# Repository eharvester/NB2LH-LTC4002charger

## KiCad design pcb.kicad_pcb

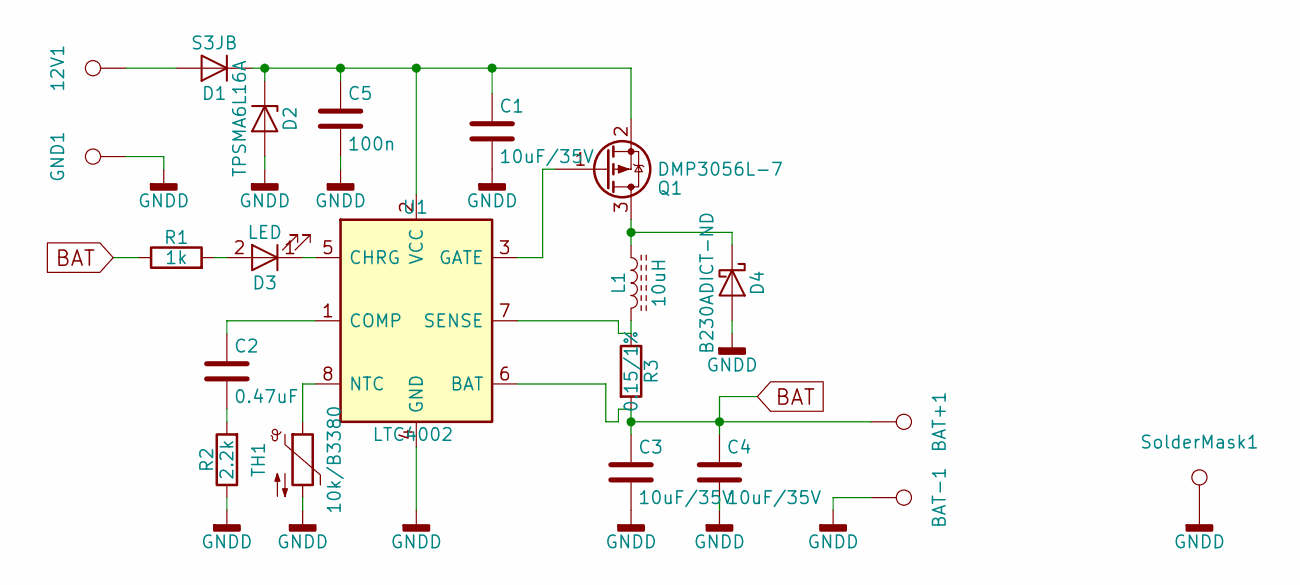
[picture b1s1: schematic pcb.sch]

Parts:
12V1: TEST_1P; TerminalPad3x8
BAT+1: TEST_1P; TerminalPad3x8
BAT-1: TEST_1P; TerminalPad3x8
C1, C3, C4: 10uF/35V; C_1206
C2: 0.47uF; C_0603
C5: 100n; C_0603
D1: S3JB; D_SMB
D2: TPSMA6L16A; D_SMA
D3: LED; R_1206_HandSoldering
D4: B230ADICT-ND; D_SMB
GND1: TEST_1P; TerminalPad3x8
L1: 10uH; L_1210
Q1: DMP3056L-7; SOT-23
R1: 1k; R_0603
R2: 2.2k; R_0603
R3: 0.15/1%; R_0603
SolderMask1: TEST_1P; SolderMask
TH1: 10k/B3380; R_1206_HandSoldering
U1: LTC4002; SOIC-8_3.9x4.9mm_Pitch1.27mm

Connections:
BAT: BAT+1.1, C3.1, C4.1, R1.1, R3.2, U1.6 (BAT)
GNDD: BAT-1.1, C1.2, C3.2, C4.2, C5.2, D2.2 (A), D4.2 (A), GND1.1, R2.1, SolderMask1.1, TH1.2, U1.4 (GND)
unnamed: 12V1.1, D1.2 (A)
unnamed: C1.1, C5.1, D1.1 (K), D2.1 (K), Q1.2 (S), U1.2 (VCC)
unnamed: C2.1, U1.1 (COMP)
unnamed: C2.2, R2.2
unnamed: D3.1 (K), U1.5 (CHRG)
unnamed: D3.2 (A), R1.2
unnamed: D4.1 (K), L1.1, Q1.3 (D)
unnamed: L1.2, R3.1, U1.7 (SENSE)
unnamed: Q1.1 (G), U1.3 (GATE)
unnamed: TH1.1, U1.8 (NTC)

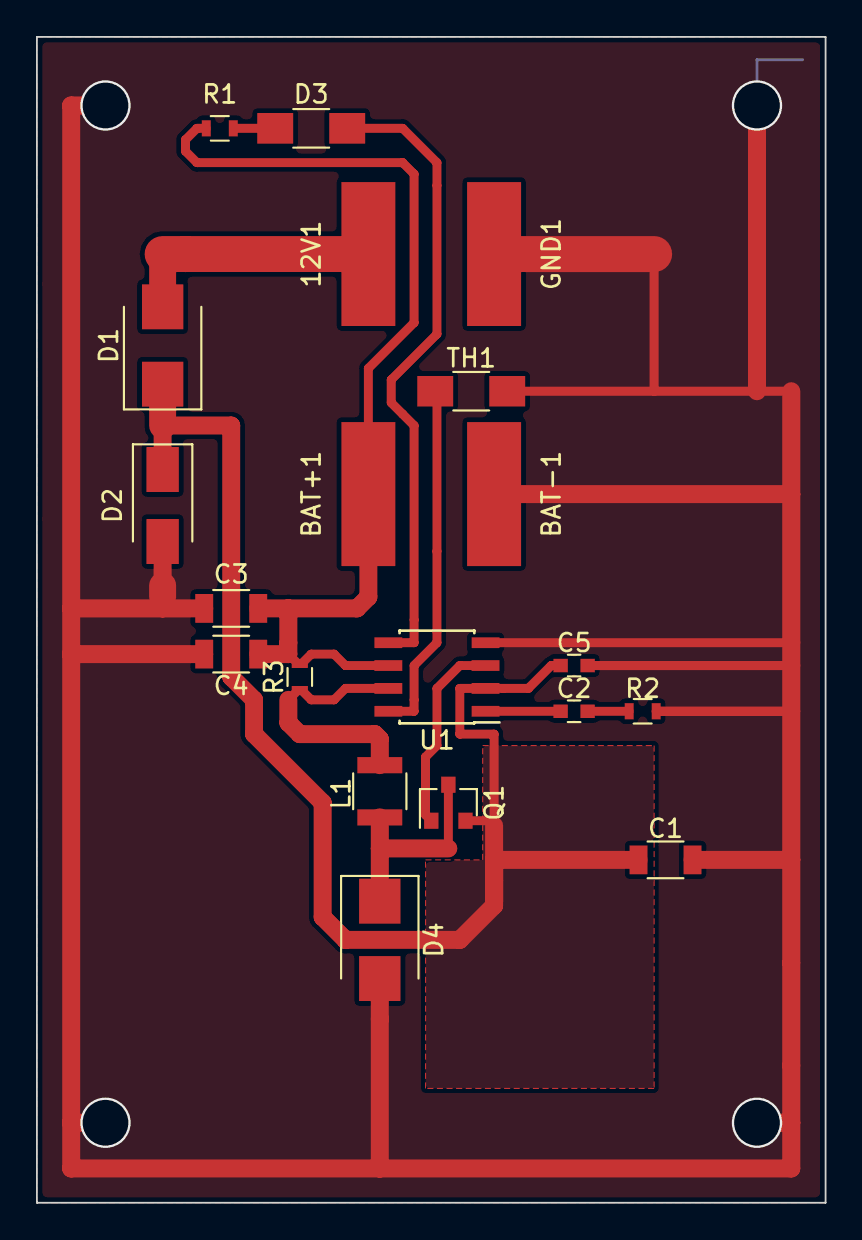
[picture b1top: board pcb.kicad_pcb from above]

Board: 2 copper layers, 43.8 x 64.8 mm, 21 parts (0 on the bottom side), 12 nets.
